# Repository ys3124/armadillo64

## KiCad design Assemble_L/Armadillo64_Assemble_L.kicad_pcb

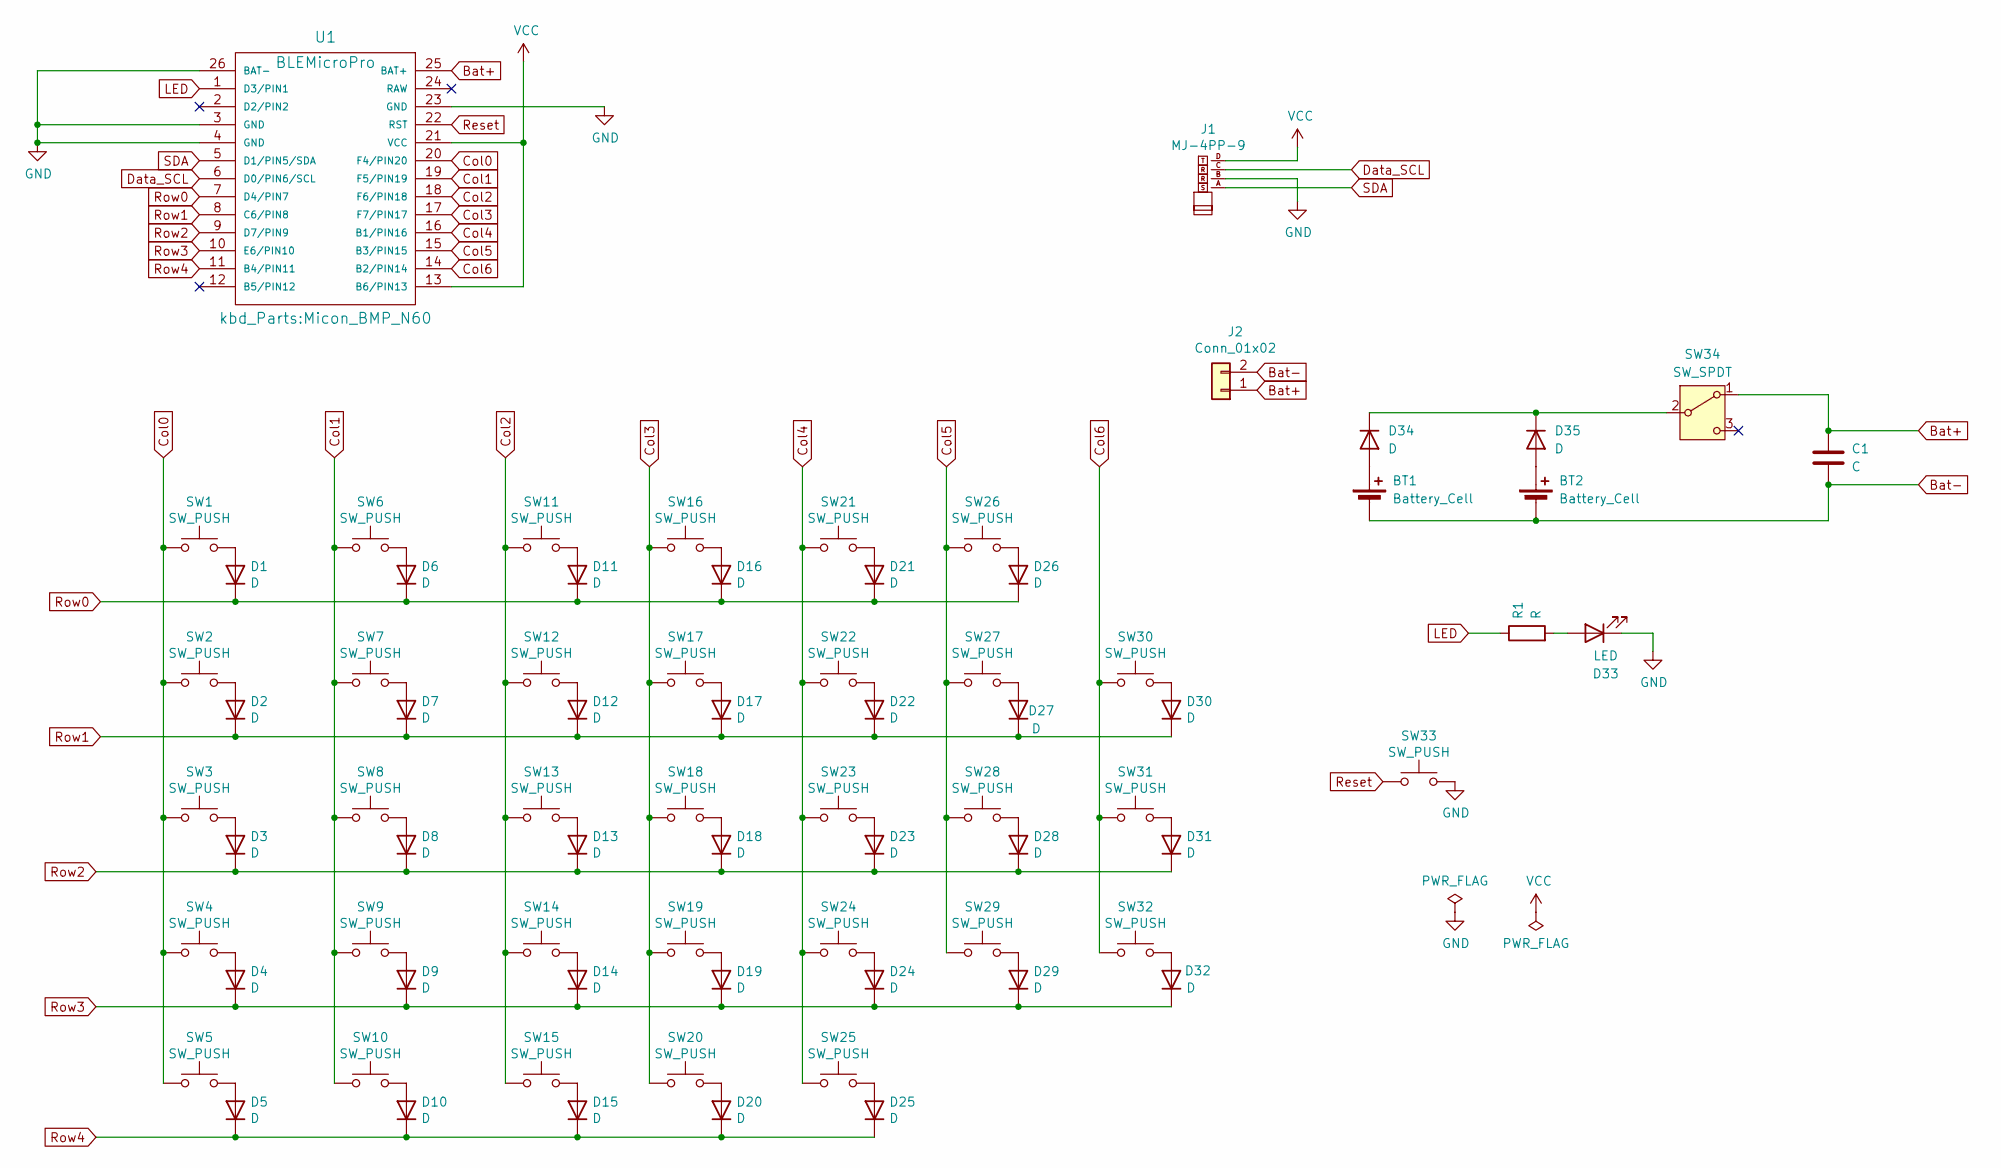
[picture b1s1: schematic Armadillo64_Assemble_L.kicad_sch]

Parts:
BT1, BT2: Battery_Cell; Battery_ali_CR1632
C1: C; Capacitor_1206
D1, D2, D3, D4, D5, D6, D7, D8, D9, D10, D11, D12, D13, D14, D15, D16, D17, D18, D19, D20, D21, D22, D23, D24, D25, D26, D27, D28, D29, D30, D31, D32, D34, D35: D; Diode_SMD
D33: LED; LED_0603_1608Metric
J1: MJ-4PP-9; TRRS_MJ-4PP-9
J2: Conn_01x02; Battery_BMP_2pin
R1: R; R_0603_1608Metric
SW1, SW2, SW5, SW6, SW7, SW8, SW9, SW10, SW11, SW12, SW13, SW14, SW15, SW16, SW17, SW18, SW19, SW20, SW21, SW22, SW23, SW24, SW25, SW26, SW27, SW28, SW29, SW30, SW31, SW32: SW_PUSH; Choc_v2_Hotswap_1u
SW3: SW_PUSH; Choc_v2_Hotswap_1.25u
SW4: SW_PUSH; Choc_v2_Hotswap_1.5u
SW33: SW_PUSH; ResetSW
SW34: SW_SPDT; TGSW_MSK-12D19
U1: BLEMicroPro; Micon_BMP_N60

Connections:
Bat+: C1.1, J2.1, SW34.1 (A), U1.25 (BAT+)
Bat-: BT1.2 (-), BT2.2 (-), C1.2, J2.2
Col0: SW1.1, SW2.1, SW3.1, SW4.1, SW5.1, U1.20 (F4/PIN20)
Col1: SW6.1, SW7.1, SW8.1, SW9.1, SW10.1, U1.19 (F5/PIN19)
Col2: SW11.1, SW12.1, SW13.1, SW14.1, SW15.1, U1.18 (F6/PIN18)
Col3: SW16.1, SW17.1, SW18.1, SW19.1, SW20.1, U1.17 (F7/PIN17)
Col4: SW21.1, SW22.1, SW23.1, SW24.1, SW25.1, U1.16 (B1/PIN16)
Col5: SW26.1, SW27.1, SW28.1, SW29.1, U1.15 (B3/PIN15)
Data_SCL: J1.C, U1.6 (D0/PIN6/SCL)
GND: D33.1 (K), J1.B, SW33.2, U1.3 (GND), U1.4 (GND), U1.23 (GND), U1.26 (BAT-)
LED: R1.1, U1.1 (D3/PIN1)
unnamed: BT1.1 (+), D34.2 (A)
unnamed: BT2.1 (+), D35.2 (A)
unnamed: D1.2 (A), SW1.2
unnamed: D2.2 (A), SW2.2
unnamed: D3.2 (A), SW3.2
unnamed: D4.2 (A), SW4.2
unnamed: D5.2 (A), SW5.2
unnamed: D6.2 (A), SW6.2
unnamed: D7.2 (A), SW7.2
unnamed: D8.2 (A), SW8.2
unnamed: D9.2 (A), SW9.2
unnamed: D10.2 (A), SW10.2
unnamed: D11.2 (A), SW11.2
unnamed: D12.2 (A), SW12.2
unnamed: D13.2 (A), SW13.2
unnamed: D14.2 (A), SW14.2
unnamed: D15.2 (A), SW15.2
unnamed: D16.2 (A), SW16.2
unnamed: D17.2 (A), SW17.2
unnamed: D18.2 (A), SW18.2
unnamed: D19.2 (A), SW19.2
unnamed: D20.2 (A), SW20.2
unnamed: D21.2 (A), SW21.2
unnamed: D22.2 (A), SW22.2
unnamed: D23.2 (A), SW23.2
unnamed: D24.2 (A), SW24.2
unnamed: D25.2 (A), SW25.2
unnamed: D26.2 (A), SW26.2
unnamed: D27.2 (A), SW27.2
unnamed: D28.2 (A), SW28.2
unnamed: D29.2 (A), SW29.2
unnamed: D30.2 (A), SW30.2
unnamed: D31.2 (A), SW31.2
unnamed: D32.2 (A), SW32.2
unnamed: D33.2 (A), R1.2
unnamed: D34.1 (K), D35.1 (K), SW34.2 (B)
unnamed: SW30.1, SW31.1, SW32.1, U1.14 (B2/PIN14)
Reset: SW33.1, U1.22 (RST)
Row0: D1.1 (K), D6.1 (K), D11.1 (K), D16.1 (K), D21.1 (K), D26.1 (K), U1.7 (D4/PIN7)
Row1: D2.1 (K), D7.1 (K), D12.1 (K), D17.1 (K), D22.1 (K), D27.1 (K), D30.1 (K), U1.8 (C6/PIN8)
Row2: D3.1 (K), D8.1 (K), D13.1 (K), D18.1 (K), D23.1 (K), D28.1 (K), D31.1 (K), U1.9 (D7/PIN9)
Row3: D4.1 (K), D9.1 (K), D14.1 (K), D19.1 (K), D24.1 (K), D29.1 (K), D32.1 (K), U1.10 (E6/PIN10)
Row4: D5.1 (K), D10.1 (K), D15.1 (K), D20.1 (K), D25.1 (K), U1.11 (B4/PIN11)
SDA: J1.A, U1.5 (D1/PIN5/SDA)
VCC: J1.D, U1.13 (B6/PIN13), U1.21 (VCC)

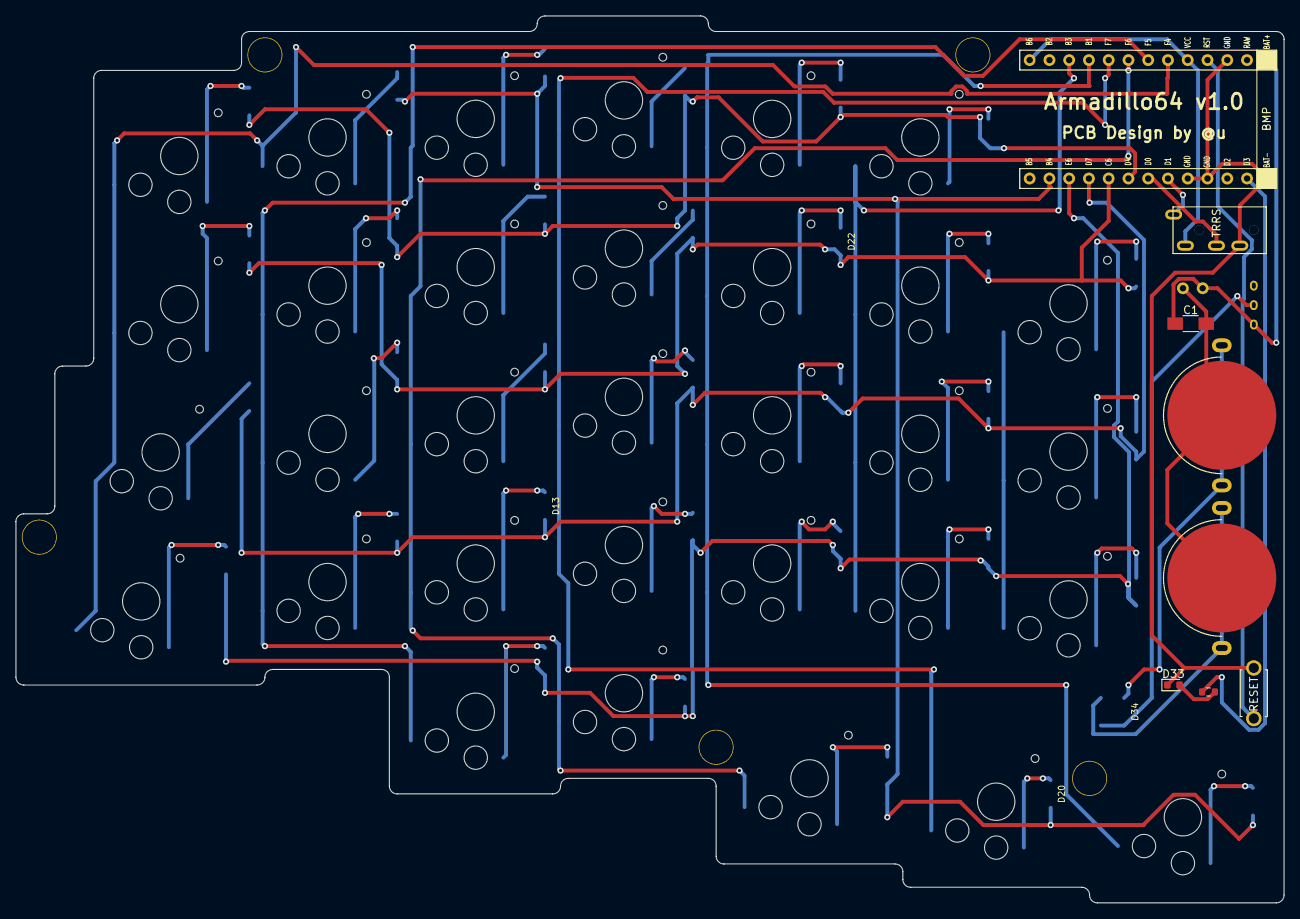
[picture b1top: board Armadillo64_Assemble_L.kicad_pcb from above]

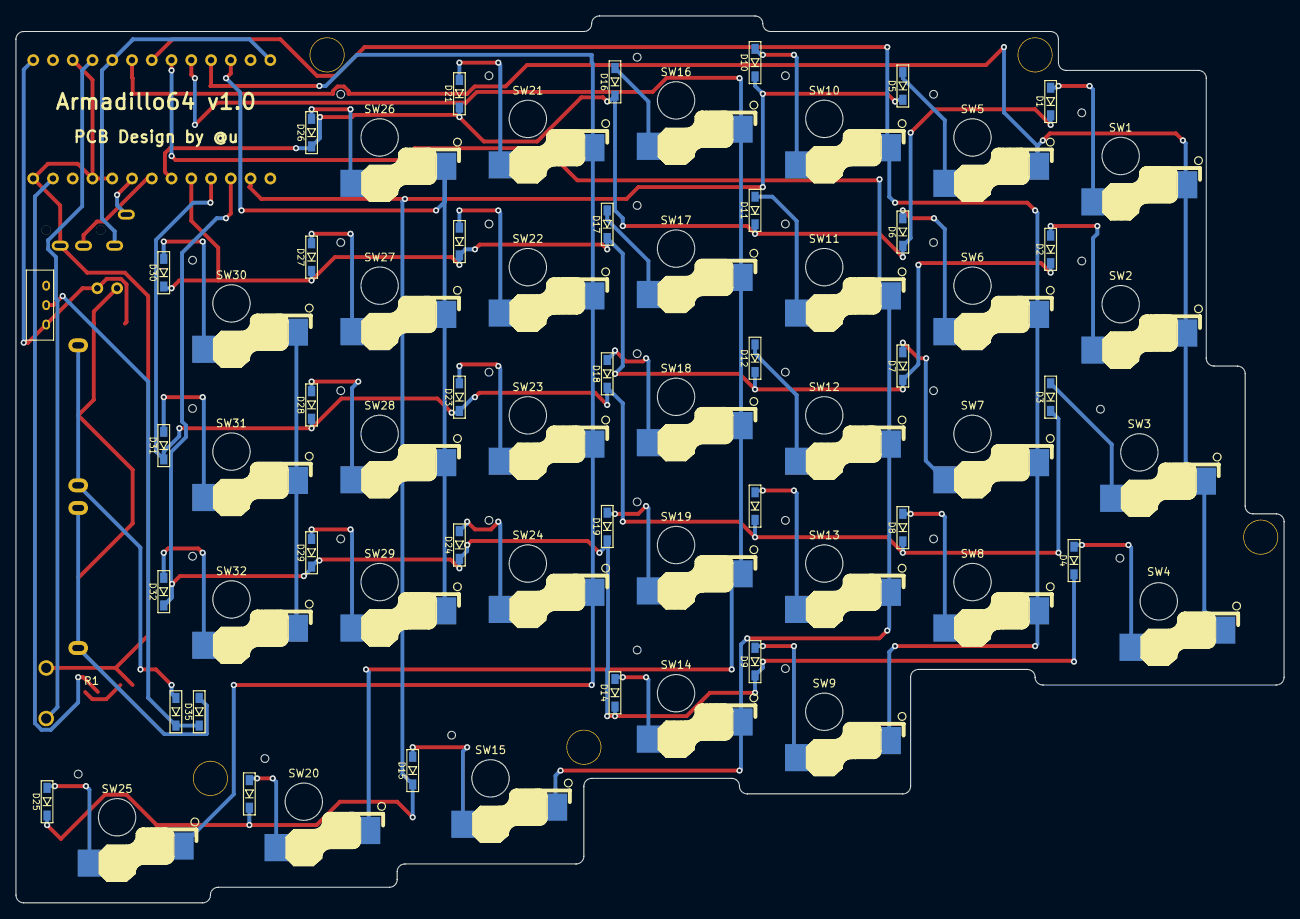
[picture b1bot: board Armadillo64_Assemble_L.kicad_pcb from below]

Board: 2 copper layers, 163.0 x 114.0 mm, 81 parts (35 on the bottom side), 56 nets.

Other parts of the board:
Ref**: Val**; m2_Spacer_Hole
Ref**#2, Ref**#3, Ref**#4, Ref**#5: Val**; m2_Spacer_Hole

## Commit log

2025-11-30 add licence.txt
